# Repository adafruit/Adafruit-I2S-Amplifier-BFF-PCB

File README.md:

## Adafruit I2S Amplifier BFF PCB

<a href="http://www.adafruit.com/products/5770"><br/>
Click here to purchase one from the Adafruit shop</a>

PCB files for the Adafruit I2S Amplifier BFF. 

Format is EagleCAD schematic and board layout
* https://www.adafruit.com/product/5770

### Description

Our QT Py boards are a great way to make very small microcontroller projects that pack a ton of power - and now we have a way for you to add an I2S 3 Watt amplifier, for high quality audio playback, that can fit on the back of your miniature dev board. It uses just three GPIO pins that do not intersect with the I2C/UART or SPI port.

We call this the Adafruit I2S Amp BFF - a "Best Friend Forever". When you were a kid you may have learned about the "buddy" system, well this product is kinda like that! A board that will watch your QT Py's back and give it more capabilities.

This PCB is designed to fit onto the back of any QT Py or Xiao board, it can be soldered into place or use pin and socket headers to make it removable. Onboard is a MAX98357 audio amplifier and picoblade-compatible connector for plugigng in a 4 or 8 ohm speaker. We use A0 for the audio data, A1 for wordselect clock, and A2 for bitclock. This pinout will work with ESP32 series, nRF52840 and RP2040 chipset boards. It won't work with the ATSAMD21 'original 'QT Py because those pins on the SAMD21 are not I2S capable. However, you could cut and rewire the traces to connect to the I2S pads if desired - personally we recommend just upgrading to an RP2040 QT Py instead.

We include some header that you can solder to your QT Py. You can also pick up an Itsy Bitsy short female header kit to make it removable but compact, you'll just need to trim down the headers to 7 pins long.

* Comes as an assembled and tested PCB
* For any QT Py or Xiao boards
* Contains a MAX98357 3 Watt audio amplifier pre-configured for 'stereo' mix output and 9 dB gain which will work great for any project.
* Connect to the speaker output with a picoblade-compatible 2-pin cable. We recommend this 3W 4 ohm speaker
* There are various Arduino / CircuitPython / MicroPython libraries can be used to talk to the I2S amplifier.

### License

Adafruit invests time and resources providing this open source design, please support Adafruit and open-source hardware by purchasing products from [Adafruit](https://www.adafruit.com)!

Designed by Limor Fried/Ladyada for Adafruit Industries.

Creative Commons Attribution/Share-Alike, all text above must be included in any redistribution. 
See license.txt for additional details.

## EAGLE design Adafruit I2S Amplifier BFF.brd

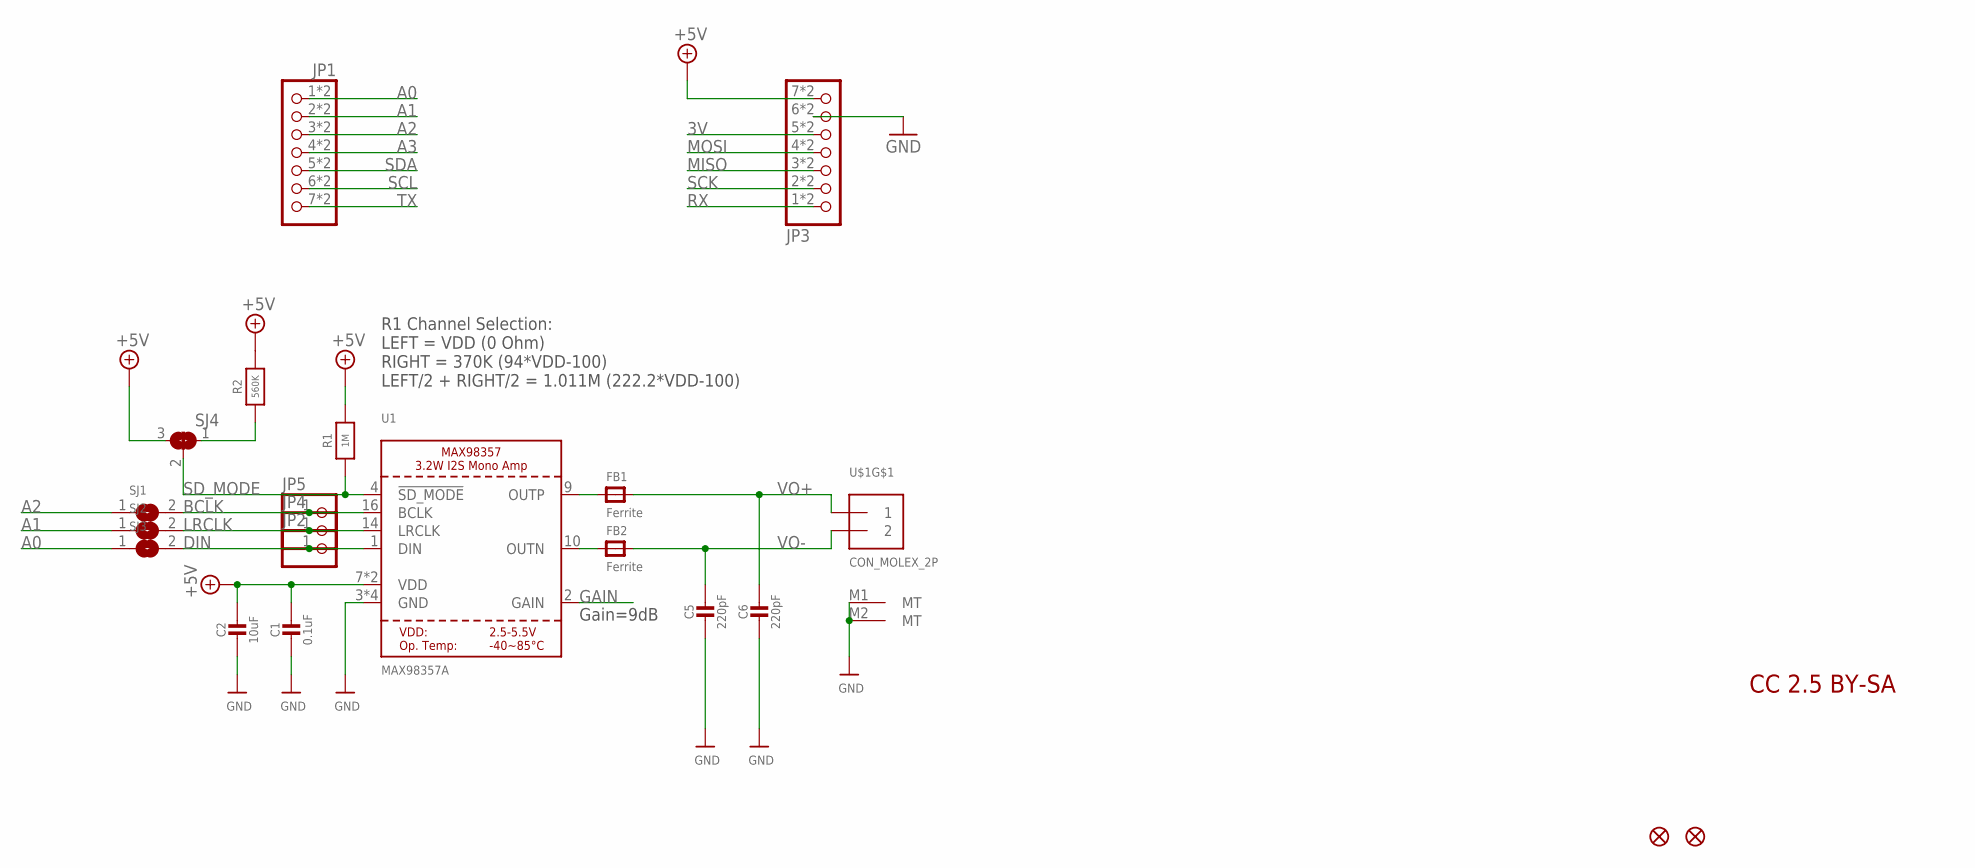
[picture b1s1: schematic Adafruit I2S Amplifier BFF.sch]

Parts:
C1: 0.1uF; 0603-NO
C2: 10uF; 0805-NO
C5, C6: 220pF; 0603-NO
FB1, FB2: Ferrite; 0603-NO
JP1, JP3: HEADER-1X7_CASTEL; 1X07_CASTEL
JP2, JP4, JP5: HEADER-1X12MM; 1X01_2MM
R1: 1M; 0603-NO
R2: 560K; 0603-NO
SJ1, SJ2, SJ3: SOLDERJUMPERCLOSED; SOLDERJUMPER_CLOSEDWIRE
SJ4: SOLDERJUMPER_2WAY; SOLDERJUMPER_2WAY_OPEN_NOPASTE
U1: MAX98357A; QFN16_3MM
U$1: CON_MOLEX_2P; 53398-0271
U$6, U$8: FIDUCIAL_1MM

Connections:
3V: JP3.5, JP3.5C (5)
+5V: C1.1, C2.1, JP3.7, JP3.7C (7), R1.2, R2.2, SJ4.3, U1.7 (VDD), U1.8 (VDD)
A0: JP1.1, JP1.1C (1), SJ3.1
A1: JP1.2, JP1.2C (2), SJ2.1
A2: JP1.3, JP1.3C (3), SJ1.1
A3: JP1.4, JP1.4C (4)
BCLK: JP5.1, SJ1.2, U1.16 (BCLK)
DIN: JP2.1, SJ3.2, U1.1 (DIN)
GAIN: U1.2 (GAIN)
GND: C1.2, C2.2, C5.2, C6.2, JP3.6, JP3.6C (6), U1.3 (GND), U1.11 (GND), U1.15 (GND), U1.THERMAL (GND), U$1.M1 (MT), U$1.M2 (MT)
LRCLK: JP4.1, SJ2.2, U1.14 (LRCLK)
MISO: JP3.3, JP3.3C (3)
MOSI: JP3.4, JP3.4C (4)
unnamed: R2.1, SJ4.1
unnamed: FB2.1, U1.10 (OUTN)
unnamed: FB1.1, U1.9 (OUTP)
RX: JP3.1, JP3.1C (1)
SCK: JP3.2, JP3.2C (2)
SCL: JP1.6, JP1.6C (6)
SDA: JP1.5, JP1.5C (5)
SD_MODE: R1.1, SJ4.2, U1.4 (!SD_MODE)
TX: JP1.7, JP1.7C (7)
VO+: C6.1, FB1.2, U$1.1
VO-: C5.1, FB2.2, U$1.2

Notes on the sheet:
CC 2.5 BY-SA
R1 Channel Selection: LEFT = VDD (0 Ohm) RIGHT = 370K (94*VDD-100) LEFT/2 + RIGHT/2 = 1.011M (222.2*VDD-100)
Gain=9dB

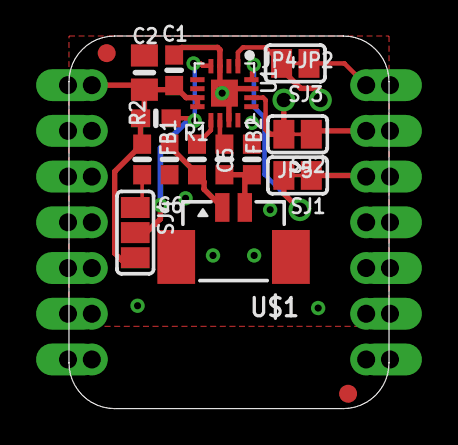
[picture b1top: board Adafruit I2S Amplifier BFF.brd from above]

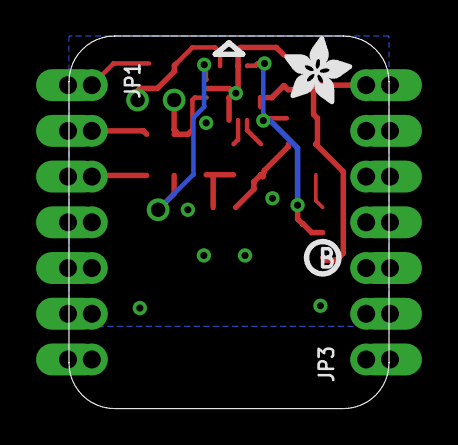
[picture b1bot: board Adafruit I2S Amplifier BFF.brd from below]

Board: 2 copper layers, 17.8 x 20.7 mm, 43 parts (10 on the bottom side), 23 nets.

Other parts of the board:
PLABEL1: PLABEL1
PLABEL2: PLABEL2
PLABEL3: PLABEL3
PLABEL4: PLABEL4
PLABEL5: PLABEL5
PLABEL6: PLABEL6
PLABEL7: PLABEL7
PLABEL8: PLABEL8
PLABEL12: PLABEL12
PLABEL14: PLABEL14
PLABEL19: PLABEL19
PLABEL20: PLABEL20
PLABEL21: PLABEL21
PLABEL22: PLABEL22
PLABEL23: PLABEL23
PLABEL24: PLABEL24
PLABEL25: PLABEL25
PLABEL26: PLABEL26
PLABEL27: PLABEL27
PLABEL28: PLABEL28
U$2: ADAFRUIT_3.5MM
U$3: PCBFEAT-REV-040

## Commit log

2023-06-14 Add board files.

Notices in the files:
parts and their libraries:
microbuilder: This work is placed in the public domain, and may be freely used for commercial and non-commercial work with the following conditions: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
